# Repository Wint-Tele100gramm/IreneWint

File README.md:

# Руслана: голосовой помощник для умного дома

Офлайн-помощник на основе [Irene Voice Assistant](https://github.com/janvarev/Irene-Voice-Assistant) (Владислав Январёв);
до переработки проект назывался «Ирина».
Сервер — ТВ-приставка на Armbian (S905 с 1 ГБ, RK3528 с 2 ГБ) или компьютер с Windows/Linux. В комнатах — клиенты на ESP32
с микрофоном и усилителем: распознавание и синтез речи идут на сервере, ответ звучит в той комнате, откуда спросили.

Распознавание (Vosk через sherpa-onnx) и голос (Silero) работают без интернета. Интернет нужен Яндекс Музыке, погоде
и нейросети Gemini.

## Что внутри

| Часть | Файлы | Что делает |
|---|---|---|
| Сервер комнат | `runva_rooms.py` | Клиенты ESP32 по WebSocket, распознавание, выбор комнаты, ответы в комнату |
| Веб-интерфейс | `web_ui.py`, `web/index.html` | Комнаты, команды, сценарии, настройки, журнал — `http://<IP сервера>:8765/` |
| Ядро | `vacore.py`, `jaa.py` | Плагины, команды, диалоги, таймеры, озвучка |
| Клиент комнаты | `esp32_client/` | Прошивка ESP32 / ESP32-S3 (Arduino IDE) |
| Плата клиента | `hardware/irene-client/` | Проект KiCad, Gerber, схема и перечень элементов: ESP32-S3 + PCM5102A + PAM8403 + 2 микрофона на одной плате 68×58 мм, детали с одной стороны |
| Мультирум | `utils/multiroom.py`, `scripts/rk3528/snapserver.conf` | Snapcast: две линии музыки, какая комната что слушает |
| Установка | `scripts/rk3528/install.sh`, `install_windows.bat`, `ruslana/` | Приставка / Windows / дополнение Home Assistant OS |

Плагины (`plugins/`, каждый — отдельный файл, лишний можно просто удалить):

| Плагин | Команды и назначение |
|---|---|
| `plugin_homeassistant` | «включи свет на кухне», «выключи весь свет», «яркость в спальне тридцать», «закрой шторы», «какая температура в детской», «сцена кино» |
| `plugin_yandex_music` | «включи музыку», «включи исполнителя …», «пауза», «дальше», «что играет», «лайк»; по комнатам: «добавь кухню», «как в спальне», «перенеси музыку на кухню», «выключи музыку везде» |
| `plugin_scenes` | свои фразы и сценарии из нескольких команд |
| `plugin_weather` | «какая погода», «погода на завтра», «на послезавтра», «в субботу», «на выходные», «прогноз на неделю», «сколько градусов на улице» — Open-Meteo, нужен интернет |
| `plugin_jokes` | «расскажи анекдот», «ещё анекдот»; «пошлый анекдот», «взрослый анекдот», «анекдот для взрослых» |
| `plugin_gemini` | всё, что не команда: «расскажи сказку про ёжика», «почему небо голубое», «а что было дальше?»; «спроси нейросеть …», «забудь разговор», «расход нейросети» — Google Gemini, бесплатный или платный тариф |
| `plugin_timer` | «таймер на пять минут», «сколько осталось», «отмени таймер» |
| `plugin_datetime` | «который час», «какое сегодня число» |
| `plugin_rooms` | «объяви …» (во всех комнатах), «громкость голоса тридцать», «какая это комната» |
| `plugin_audio_sources` | «режим сопряжения», «блютуз на кухне» — звук с телефона (Bluetooth, DLNA) по комнатам (Linux) |
| `plugin_greetings`, `plugin_random`, `plugin_gamemoreless`, `plugin_voiceover` | «привет», «подбрось монетку», игра «больше-меньше», «скажи …» |
| `plugin_tts_silero`, `plugin_tts_console` | голос Silero; текст в консоль, если голос не загрузился |
| `plugin_fuzzy` | нечёткое сравнение команд: «вкличи свет», «какая пагода», «включи мою вону» — находит ближайшую команду (настройки: `options/plugin_fuzzy.json`, порог `threshold`) |
| `plugin_playwav_aplay`, `plugin_playwav_sounddevice` | проигрывание на Linux / Windows |
| `plugin_normalizer_prepare` | числа, латиница и символы — в слова для озвучки |

Как написать свой плагин: [docs/PLUGINS.md](docs/PLUGINS.md).
Из форка [AlexeyBond](https://github.com/AlexeyBond/Irene-Voice-Assistant) взяты идеи диалогов на генераторах, сценариев,
очистки кэша озвучки, записи звука для отладки и произношение времени с падежами (`utils/ru_speech`).

## Установка

**Приставка (Armbian/Debian, aarch64):**
```bash
git clone -b rk3528 https://github.com/Wint-Tele100gramm/IreneWint.git ~/irene
cd ~/irene
bash scripts/rk3528/install.sh     # Python берётся системный (3.10+) или PYTHON=/путь/к/python3
```
Параметры: `--no-bt`, `--no-dlna`, `--no-multiroom`, `--aec` (эхоподавление), `--lite` / `--full`.
Повторный запуск обновляет установку (AirPlay от прежних версий удаляется).
Python должен быть собран с `ssl`, `ctypes`, `sqlite3` — скрипт это проверит.

**Windows 10/11:** [README_WINDOWS.md](README_WINDOWS.md).

**Home Assistant OS (дополнение):** Настройки → Дополнения → Магазин дополнений → ⋮ → Репозитории →
`https://github.com/Wint-Tele100gramm/IreneWint#rk3528`, затем установить «Руслана». Сервер работает на машине
с Home Assistant, устройства Home Assistant подключаются сами, веб-интерфейс — в боковой панели. Подробно и чем
отличается от приставки — [ruslana/DOCS.md](ruslana/DOCS.md).

Дальше всё настраивается в веб-интерфейсе `http://<IP сервера>:8765/` (пароль — ключ клиентов,
`token` в `options/rooms.json`; установщик его покажет).

**Где настройки.** Все — в папке `options/`: `core.json` (ассистент), `rooms.json` (сервер комнат и ключ клиентов),
`plugin_*.json` (по файлу на плагин). Значения по умолчанию заданы в коде; файлы создаются сами при первом запуске
и хранят только ваши настройки — менять их удобнее на странице Русланы. Папка `options/` не попадает в git
(в ней токены), обновление `git pull` её не трогает.

## Веб-интерфейс

- **Комнаты** — клиенты на связи, прошивка, Wi-Fi, обрывы, причина перезагрузки; назначение комнаты (зоны Home Assistant
  из списка), громкость голоса, уровни речи; у микрофона самого сервера — усиление и живой индикатор.
  Сверху — что играет на линиях музыки; в карточке комнаты — какую линию она слушает и громкость музыки.
  Внизу — «Прошивка клиентов»: загрузить `IreneClient.ino.bin` и обновить клиенты по Wi-Fi (с откатом, если не заработает).
- **Команды** — команда текстом в любой комнате, последние услышанные фразы, список команд.
- **Сценарии** — редактор сценариев и своих фраз, работает сразу.
- **Настройки** — имена помощника, голос («Послушать»), Home Assistant, вход в Яндекс Музыку по коду
  (только с правами Музыки), время, таймер, сервер. Нужен перезапуск — появится кнопка.
- **Журнал** — события сервера, выбор устройств Home Assistant, записи фраз.

Страница для домашней сети: порт 8765 в интернет не открывайте. Выключить: `"web_ui": false` в `options/rooms.json`.

## Home Assistant

Токен: HA → Профиль → Безопасность → Долгосрочные токены доступа. Адрес и токен — в «Настройках» веб-интерфейса.

- Устройства ищутся по имени и зоне HA. Если названа комната, поиск идёт только в этой зоне; реле света ZHA (домен
  `switch`) тоже считаются светом. Что именно выбрано — видно в «Журнале».
- Без комнаты в команде берётся комната клиента: «включи свет» в спальне включит свет в зоне «Спальня».
- Одинаковые устройства в разных комнатах — Руслана переспросит: «Люстру где: Кухня или Спальня?»
- Устройство без связи (Zigbee) — Руслана так и скажет, а не отчитается впустую.
- Неудобное имя — синоним в `options/plugin_homeassistant.json`:
  `"aliases": { "ночник": "light.0x00158d0001a2b3c4", "свет в зале": ["light.a", "light.b"] }`.

## Погода

Плагин `plugin_weather` берёт прогноз с [Open-Meteo](https://open-meteo.com/): бесплатно, без ключа и регистрации,
но нужен интернет. В «Настройках» веб-интерфейса (раздел «Погода») укажите город — координаты найдутся сами
при первом вопросе — или широту и долготу дома (Яндекс Карты: правый клик по дому). Прогноз хранится
15 минут; если сервер недоступен, Руслана ответит по последнему прогнозу (не старше 6 часов).

Что можно спросить: «какая погода» (сейчас и на сегодня), «погода сегодня», «погода на завтра»,
«на послезавтра», «погода в пятницу», «в следующий понедельник», «на выходные», «прогноз на неделю»,
«сколько градусов на улице», «будет ли дождь завтра».

## Анекдоты

Плагин `plugin_jokes`: «расскажи анекдот» — обычный, «пошлый анекдот», «взрослый анекдот», «анекдот для
взрослых» — пошлый. «Ещё анекдот» сразу после пошлого — ещё пошлый. Руслана не повторяется, пока не расскажет
все анекдоты набора.

Анекдоты скачивает `scripts/get_jokes.py` (его вызывает `install.sh`; вручную:
`.venv/bin/python scripts/get_jokes.py`) в `data/jokes.json`. Источник — датасет
[igorktech/anekdots](https://huggingface.co/datasets/igorktech/anekdots) (лицензия ODC-BY, тексты с anekdot.ru),
самые высоко оценённые читателями; запасной — rzhunemogu.ru (`--source rzhunemogu`). Обычные и пошлые
разделяются по словам-признакам (мат — тоже в пошлые). Отбрасываются пошлые анекдоты, где есть дети,
анекдоты на национальные и прочие оскорбительные стереотипы, слишком длинные и с латиницей.
Сколько брать: `--normal 5000 --adult 2000`.

Hugging Face помечает этот датасет как «Not-For-All-Audiences» и без входа в аккаунт может его не отдать.
Тогда скачайте файл вручную (на странице датасета нажмите «View content», вкладка «Files», файл `anekdots.json`
или parquet-файл, сконвертированный в JSON), положите его на приставку, например в `data/anekdots.json`,
и запустите `.venv/bin/python scripts/get_jokes.py --file data/anekdots.json`. Подходят JSON-массив, JSON Lines,
«словарь столбцов» (`{'total_mark': [...], 'text': [...]}`, в том числе с кавычками Python) и `.gz`; файл читается потоком, памяти нужно ~50 МБ.

Пошлые можно выключить совсем или только в некоторых комнатах (раздел «Анекдоты» в «Настройках»).

## Нейросеть (Gemini)

Плагин `plugin_gemini` отвечает на фразы, для которых у Русланы нет команды: сказки, вопросы, разговор.
Команды (свет, музыка, таймер, погода…) по-прежнему выполняет сама Руслана, нейросеть их не перехватывает.
Явно: «спроси нейросеть …». Настройки — «Настройки» → «Нейросеть (Gemini)».

- Ключ: [aistudio.google.com/apikey](https://aistudio.google.com/apikey).
- Из России Google API отвечает «User location is not supported»: нужен прокси в другой стране
  (`socks5h://адрес:порт` или `http://адрес:порт`) или свой ретранслятор в поле «Адрес API».
- **Бесплатный тариф**: ограничение запросов в минуту и в день; когда лимит основной модели исчерпан, Руслана
  повторяет вопрос запасной (`gemini-flash-lite-latest`). Google может использовать такие запросы для обучения.
- **Платный тариф**: в AI Studio привязать к проекту ключа платёжный аккаунт (Billing) и выбрать «Платный»
  в настройках. Лимиты выше, можно взять модель сильнее (например Pro) и включить «размышления», запросы
  не идут в обучение. Расход токенов считается по месяцам (`data/gemini_usage.json`, «Руслана, расход нейросети»),
  есть месячный лимит. Подписка Google AI Pro / Gemini Advanced — для приложения Gemini, к API отношения не имеет.
- Ответ звучит в той комнате, где спросили, по предложениям; пока нейросеть думает, другие команды работают.
  Если ответа нет дольше 3 с, Руслана скажет «Сейчас подумаю».
- Разговор помнится 5 минут по каждой комнате: «а что было дальше?». «Забудь разговор» — сначала.
- Вопрос и ответ видны в «Журнале». Текст запросов уходит в Google.

## Яндекс Музыка

Вход — кнопкой в «Настройках» (код вводится на ya.ru/device) или `.venv/bin/python scripts/rk3528/yandex_token.py`.
Запрашиваются только права Музыки. Нужна подписка Плюс. Пока Руслана слушает команду или отвечает, музыка приглушается.

### Музыка по комнатам (мультирум)

Snapcast (ставит `install.sh`) держит **две независимые линии музыки**: например, у вас в комнате одна, у жены — другая.
Комнаты с музыкой — клиенты ESP32 с прошивкой 3.1+ и динамик приставки (snapclient с ID `local`). В одной линии
комнаты играют синхронно. Звук — 44100 Гц стерео (≈1,4 Мбит/с Wi-Fi на комнату), задержка 0,6 с: пауза и «стоп»
слышны сразу (клиенты приглушаются мгновенно), «дальше» — меньше чем через секунду.

После обновления с прошивки 3.0: `git pull && bash scripts/rk3528/install.sh` (новый `snapserver.conf`) и прошивка 3.1
во всех клиентах — старая стерео-поток не играет. Если в комнатах прерывается музыка, в
`~/.config/irene/snapserver.conf` увеличьте `buffer` до 1000.

| Сказать | Что будет |
|---|---|
| «включи музыку», «поставь кино» | играет там, где сказали. Если здесь уже играла своя музыка — заменяется |
| «включи музыку на кухне», «…везде» | в названных комнатах (если здесь уже играет — комнаты подключаются к этой музыке) |
| «добавь кухню», «и в спальне», «музыку везде» | комнаты подключаются к музыке этой комнаты |
| «как на кухне», «то же, что в спальне» | эта комната слушает то же, что там |
| «перенеси музыку на кухню» | музыка уходит отсюда туда |
| «выключи музыку» | здесь (если эту музыку слушают и в других комнатах — они продолжают) |
| «выключи музыку на кухне», «…везде», «выключи всю музыку» | там / везде |
| «где играет музыка» | что играет на каждой линии и в каких комнатах |
| «громче», «тише», «громкость тридцать» | громкость музыки в этой комнате |
| «пауза», «дальше», «что играет», «лайк» | для музыки этой комнаты (или единственной играющей) |

Обе линии заняты, а новую музыку просят в третьей комнате — Руслана скажет, что где играет, и предложит «как на …».
То же самое — на странице «Комнаты». Без snapserver (Windows, `--no-multiroom`) музыка играет на динамике сервера.

Клиенты старых прошивок (до 3.1) музыку не играют. На ESP32-S3 с прошивкой 3.1 эхоподавление убирает музыку из микрофона;
на обычном ESP32 микрофон слышит её:
говорите «Руслана» громче музыки — после имени музыка в комнате притихнет до конца команды.

## Звук с телефона (приставка)

| Откуда | Как |
|---|---|
| Android и iOS | «Руслана, режим сопряжения» → в Bluetooth телефона выбрать **Ruslana** (3 минуты) |
| Android | Приложение с DLNA/UPnP (BubbleUPnP, Hi-Fi Cast) → «Руслана» |

С мультирумом звук с телефона идёт не в динамик приставки, а в третью линию — **«Телефон»** (поток `phone`
в snapserver; PipeWire получает выход «Ruslana-rooms», и всё, что приходит по Bluetooth и DLNA, перенаправляется в него):

- телефон заиграл — звук идёт в комнату, где сказали «режим сопряжения» (или туда, где слушали в прошлый раз);
- «Руслана, блютуз на кухне», «телефон везде», «музыку с телефона» — подключить комнаты; «добавь спальню»,
  «как на кухне», «выключи музыку» — как с Яндекс Музыкой; на странице «Комнаты» — линия «Телефон»;
- «пауза», «продолжи», «дальше», «назад», «что играет» — управляют телефоном по Bluetooth (AVRCP);
- телефон молчит 20 секунд — комнаты линии выключаются.

Нужна новая настройка snapserver: после обновления запустите `bash scripts/rk3528/install.sh`. Если PipeWire не создаст
выход (в журнале «не создал выход в комнаты»), звук с телефона играет на динамике приставки, как раньше.

Встроенный Bluetooth приставок часто не поддерживается ядром Armbian — подойдёт USB-донгл (RTL8761B).

## Комнаты

- Клиент: [esp32_client/README.md](esp32_client/README.md). Название комнаты = зона в Home Assistant
  (можно назначить на странице «Комнаты», не трогая клиент).
- Одну фразу услышали несколько клиентов — ответит тот, где громче; команда выполнится один раз.
- Таймеры и их сигнал звучат в той комнате, где их поставили; если клиент отключился — во всех комнатах.
- Микрофон самого сервера тоже может быть комнатой: «Микрофон приставки как комната» в настройках.
- Распознавание работает, только пока в комнате говорят — 5–6 комнат не нагружают сервер постоянно.

### Сценарии

На странице «Сценарии» или в `options/plugin_scenes.json`:
```json
{
    "aliases": { "зажги|сделай светло": "включи свет" },
    "scenes": {
        "спокойной ночи": ["выключи весь свет", "выключи музыку", "скажи: Спокойной ночи!"],
        "доброе утро": ["включи свет на кухне", "время", "какая погода", "включи музыку"]
    },
    "quiet_steps": true
}
```
Шаг — любая команда, `скажи: текст` или `пауза: секунды`. Свои фразы важнее одноимённых встроенных команд.

### Диалоги в своих плагинах

Команда может вернуть генератор: `answer = yield "Вопрос?"` (или `yield ("Вопрос?", 15)` с таймаутом).
Ответ ждётся без имени и в той же комнате; без ответа в генератор придёт `DialogTimeout` (`from vacore import DialogTimeout`).

## Распознавание, голос, кэш

- Распознавание: малая потоковая модель Vosk int8 — ~100 МБ ОЗУ на все комнаты.
  `bash scripts/rk3528/get_asr_model.sh full` — полная 0.56 (~250 МБ ОЗУ, точнее; для 2 ГБ и больше).
- Голос: Silero TTS (`v5_5_ru`, PyTorch): естественная речь с ударениями, «ё», омографами и вопросительной
  интонацией. Голоса xenia, baya, kseniya (женские), aidar, eugene (мужские) — на странице Русланы, раздел «Голос».
  Ставит `install.sh` (`scripts/rk3528/get_tts_silero.sh`: PyTorch для процессора и модель в `models/silero`),
  скорость на этой машине: `.venv/bin/python scripts/tts_bench.py --threads 2 3` при остановленной Руслане.
  Ответ звучит по предложениям: первое начинает играть, пока синтезируются следующие.
  Память — 450–650 МБ; на 1 ГБ работает со сжатой подкачкой zram. Лицензия моделей — CC BY-NC 4.0 (для дома можно).
- Частота процессора: пока клиент передаёт фразу и пока синтезируется ответ, регулятор частоты переключается
  на `performance` (ядра сразу на максимуме), через 3 с после речи возвращается прежний (ondemand / schedutil).
  Права на это даёт `install.sh` (`/etc/tmpfiles.d/irene-cpufreq.conf`). Выключить или изменить задержку —
  «Настройки» → «Сервер и клиенты». Проверить: `watch -n0.5 cat /sys/devices/system/cpu/cpufreq/policy0/scaling_governor`.
- Кэш ответов (`tts_cache/`) чистится раз в 6 часов: не больше 300 МБ и без фраз, не звучавших 90 дней.
- Запись фраз для отладки: «Записывать фразы в WAV» в настройках — слушать на вкладке «Журнал».

## Эхоподавление на приставке

```bash
bash scripts/rk3528/enable_aec.sh        # включить
bash scripts/rk3528/enable_aec.sh off    # выключить
```
PipeWire вычитает звук динамика из микрофона приставки: Руслану можно перебить («стоп», «хватит»), а «Руслана, …» слышно поверх
музыки. Перед включением выберите реальные микрофон и динамик по умолчанию (`pactl set-default-source/sink`).

## Приставка с 1 ГБ ОЗУ

`install.sh` сам включает облегчённый режим при ОЗУ меньше 1,5 ГБ: без DLNA и Bluetooth, zram-подкачка, лимит памяти
Русланы 800 МБ. Ориентировочно: распознавание ~100 МБ, голос ~250 МБ, mpv (на каждую играющую линию) ~40 МБ,
PipeWire + snapserver + snapclient ~60 МБ.

## Управление

```bash
systemctl --user restart irene          # перезапуск (или кнопкой в веб-интерфейсе)
journalctl --user-unit irene -f         # логи
systemctl --user status irene-snapserver irene-snapclient   # мультирум
.venv/bin/python scripts/rk3528/irene_cmd.py "руслана который час"   # команда текстом из консоли
```

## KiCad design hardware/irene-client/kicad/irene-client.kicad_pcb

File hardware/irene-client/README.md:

# Плата клиента Русланы v3

Весь клиент на одной двухсторонней плате **68×58 мм**: ESP32-S3, стереоЦАП PCM5102A, усилитель PAM8403 2×3 Вт,
разъёмы для двух микрофонов INMP441. **Все детали — на верхней стороне** (SMD и штыри в отверстия), нижний слой —
земля и немногие перемычки. Питание 5 В на штыри, все стабилизаторы и фильтры на плате. Разъёма USB нет: первая
прошивка — проводами к выводам модуля, дальше — по Wi-Fi.

Версия 3 рассчитана на изготовление и дома (ЛУТ, фоторезист):

| | v2 | v3 |
|---|---|---|
| Размер | 50×42 мм | 68×58 мм |
| Детали | с обеих сторон | только сверху |
| Дорожки | 0,25–0,6 мм | сигналы 0,6 мм, питание 0,8 мм (≈70 % длины не уже 0,6 мм) |
| Зазор | 0,2 мм | 0,4 мм (кроме выводов ЦАП и LP5907, см. ниже) |
| Переходы | 58 + 26 сшивки земли, 0,6/0,3 мм | 34, 1,4/0,6 мм — под проволочную перемычку |
| Переходы под деталями | были | нет ни одного |
| Медь меньше 1 мм² и островки без земли | были | убраны |

| Сверху | Снизу |
|---|---|
|  |  |

Картинки сделаны из готовых Gerber-файлов (вид снизу — зеркальный, как если перевернуть плату).

## Файлы

| Файл | Что это |
|---|---|
| `kicad/` | **проект KiCad**: схема, плата с разводкой и заливками, правила (зазоры) |
| `irene-client.lay6` | **плата для Sprint Layout 6** (см. ниже) |
| `irene-client-gerber.zip` | Gerber + сверловка, собранные генератором (для заказа без KiCad) |
| `schematic.pdf` | принципиальная схема (A3) |
| `img/assembly-top.png`, `img/assembly-bottom.png` | сборочный чертёж: где какая деталь, номиналы, первый вывод — красная точка |
| `bom.csv` | перечень элементов (Excel, разделитель «;») |
| `bom-jlcpcb.csv`, `cpl-jlcpcb.csv` | перечень и координаты деталей (обе стороны) в формате JLCPCB для заводского монтажа |

## Проект KiCad

Открыть `kicad/irene-client.kicad_pro` в KiCad 7, 8 или 9 (проект в формате KiCad 6, новая версия сама предложит его
обновить). Библиотеки ставить не нужно: символы и посадочные места лежат внутри файлов.

1. **Плата** (`irene-client.kicad_pcb`): нажать **B** — KiCad зальёт землю на обоих слоях (заливки заданы, но в файле не
   залиты). Затем «Проверка → Проверка правил проектирования (DRC)».
2. **Правила** (класс Default и файл `irene-client.kicad_dru`): зазор между дорожками, площадками и переходами разных
   цепей — 0,4 мм. Исключения — выводы с мелким шагом: у PCM5102A (TSSOP, шаг 0,65 мм) и LP5907 (SOT-23-5) зазор до
   выводов 0,2 мм, между дорожками цепей ЦАП у его выводов — 0,3 мм; дорожки к выводам ЦАП — 0,3 мм (шире вывода
   не бывают). Ширина остальных: сигналы 0,6 мм, питание 5 В и динамики — 0,8 мм; там, где 0,6 мм не помещается
   (около ЦАП, между выводами), дорожка уже — но не уже 0,3 мм. Переходы 1,4/0,6 мм, ни одного под корпусами деталей
   (это проверяет генератор по контуру корпуса — в правилах KiCad по курсу этого не выразить).
3. **Gerber**: «Файл → Изготовление → Gerber» (слои F/B.Cu, F/B.Paste, F/B.Silkscreen, F/B.Mask, Edge.Cuts) и
   «Сверловка» — сжать в zip и загрузить на сайт фабрики.
4. Схема (`irene-client.kicad_sch`) связана с платой: «Обновить плату по схеме» (F8) не должна предлагать изменений,
   кроме служебных.

## Sprint Layout 6

`irene-client.lay6` — та же плата для Sprint Layout 6.0: детали как компоненты (позиционное обозначение и номинал —
в свойствах детали), площадки, дорожки, переходы, шелкография с подписями, контур, запрет массива под антенной.

- Заливка земли — «массив» Sprint Layout, включён на обоих слоях; Sprint Layout рассчитывает его сам.
  Дорожки, переходы и SMD-выводы цепи GND подключены к массиву сплошь, выводы штырей — термобарьером 0,5 мм,
  у остальных объектов зазор до массива 0,4 мм.
- Там, где генератор убрал медь (островки без связи с землёй и куски меньше 1 мм²), стоят вырезы массива —
  Sprint Layout их не зальёт. Земля разведена и дорожками, поэтому связь всех её выводов от массива не зависит.
- Цепей (связей) в формате Sprint Layout нет — только медь; соединения проверены в генераторе.
- Файл собран по описанию формата из KiCad (импорт Sprint Layout); чтение и запись сверены побайтово с файлами,
  сохранёнными самим Sprint Layout, но в самой программе файл не открывался. Если что-то откроется не так —
  в Sprint Layout 6 есть «Файл → Импорт → Gerber»: подойдут файлы из `irene-client-gerber.zip`.

## Штыри на плате

| Разъём | Выводы (по шелкографии) | Что подключать |
|---|---|---|
| J1 | 5V, G | блок питания 5 В, 2 А (5V — квадратная площадка) |
| J5 | R+ R− L− L+ | динамики 4–8 Ом. Минусы динамиков с землёй **не соединять** (выходы мостовые) |
| J3 «MIC1» | G V SD SC WS G | микрофон 1 INMP441: GND, VDD, SD, SCK, WS, L/R (L/R уже на земле) |
| J4 «MIC2» | G V SD SC WS V | микрофон 2 INMP441: то же, L/R уже на 3,3 В (правый канал). Разъём повёрнут: вывод 1 (G) — снизу |

Провода к микрофонам — до 20–30 см, лучше витой парой или в общей оплётке с землёй.

## Первая прошивка без USB-разъёма

Подпаяться тонкими проводами к выводам модуля U1 (нумерация — по сборочному чертежу, вывод 1 — красная точка):

- **через USB**: вывод 14 — D+ (зелёный провод USB), вывод 13 — D− (белый), земля — любой вывод G, питание — 5 В на J1.
  В Arduino IDE: плата «ESP32S3 Dev Module», **USB CDC On Boot: Enabled**, остальное — как в `esp32_client/README.md`;
- **или через переходник USB-UART на 3,3 В**: вывод 37 (TXD0) → RX переходника, вывод 36 (RXD0) → TX, GND → GND.

Вход в загрузчик: держать BOOT, нажать и отпустить RST, отпустить BOOT. После первой прошивки провода снять —
дальше обновления идут по воздуху («Прошивка клиентов» в веб-интерфейсе сервера).

## Схема вкратце

- **Вход 5 В**: самовосстанавливающийся предохранитель 2 А → защита от переполюсовки (P-MOSFET AO3401A) →
  TVS-диод 6 В → 220 мкФ.
- **3,3 В для ESP32 и микрофонов** — AMS1117-3.3; микрофоны дополнительно через RC-фильтр 10 Ом + 10 мкФ.
- **3,3 В для аналоговой части ЦАП** — отдельный малошумящий LP5907; цифровая часть ЦАП — через ферритовую бусину.
- **Усилитель** питается отдельной веткой: дроссель 4,7 мкГн + 470 мкФ рядом с микросхемой. Импульсный ток
  усилителя не идёт через цифровую часть — то, что раньше давал аккумулятор 18650.
- **Земля** — дорожками ко всем выводам и заливка поверх на обоих слоях; под ЦАП и усилителем — дорожка по оси корпуса
  от их земляных выводов. Под антенной модуля меди нет на обоих слоях.
- **ЦАП и усилитель включает прошивка** (GPIO 17 → XSMT ЦАП и SHDN усилителя): в тишине они выключены — нет шипения.
- Делитель 10к/1,2к на входе PAM8403: полной громкости соответствует почти полная мощность усилителя без перегрузки.

GPIO: микрофоны SCK 4, WS 5, SD 6; ЦАП DIN 7, BCK 15, LRCK 16; включение ЦАП и усилителя 17; светодиод 18;
кнопка BOOT — GPIO 0. Те же, что в прошивке (`esp32_client/IreneClient/config.h`, с версии 3.4).

## Заказ и сборка

- **Заказ**: 2 слоя, 1,6 мм, 68×58 мм; минимальная дорожка 0,3 мм, зазор 0,2 мм (у выводов ЦАП), отверстия от 0,6 мм.
  Покрытие HASL lead free или ENIG.
- **Дома** (ЛУТ / фоторезист): вывод на плёнку — из Gerber или из Sprint Layout. Переходы — проволочные перемычки
  (отверстие 0,6 мм, площадка 1,4 мм): все стоят вне корпусов деталей, их можно паять до установки деталей.
  Самое тонкое место — веер дорожек 0,3 мм у ЦАП (шаг выводов 0,65 мм).
- **Заводской монтаж** (по желанию): загрузить `bom-jlcpcb.csv` и `cpl-jlcpcb.csv`, монтаж с одной стороны (Top).
  Поворот деталей в предпросмотре иногда приходится поправить вручную.
- **Ручная сборка**: перемычки в переходах, затем микросхемы с мелким шагом (U3, U5), стабилизаторы, пассивные,
  дроссель, диод, электролиты, кнопки, модуль ESP32, в конце штыри.
  До установки модуля подать 5 В на J1 через резистор 10–20 Ом и проверить 3,3 В на выходах AMS1117 и LP5907.

## Как пересобрать

Всё генерируется скриптами из `hardware/gen` (детали и цепи — `design.py`, расстановка — `placement.py`):

```
IRENE_PCB_EXT=<папка с kiutils, библиотеками KiCad и freerouting> python3 hardware/gen/build.py [--route] [--reuse]
```

Скрипт сам проверяет результат: связность всех цепей и отсутствие замыканий — по готовым Gerber; зазоры — по разводке;
цепи схемы KiCad — по сравнению с `design.py`.

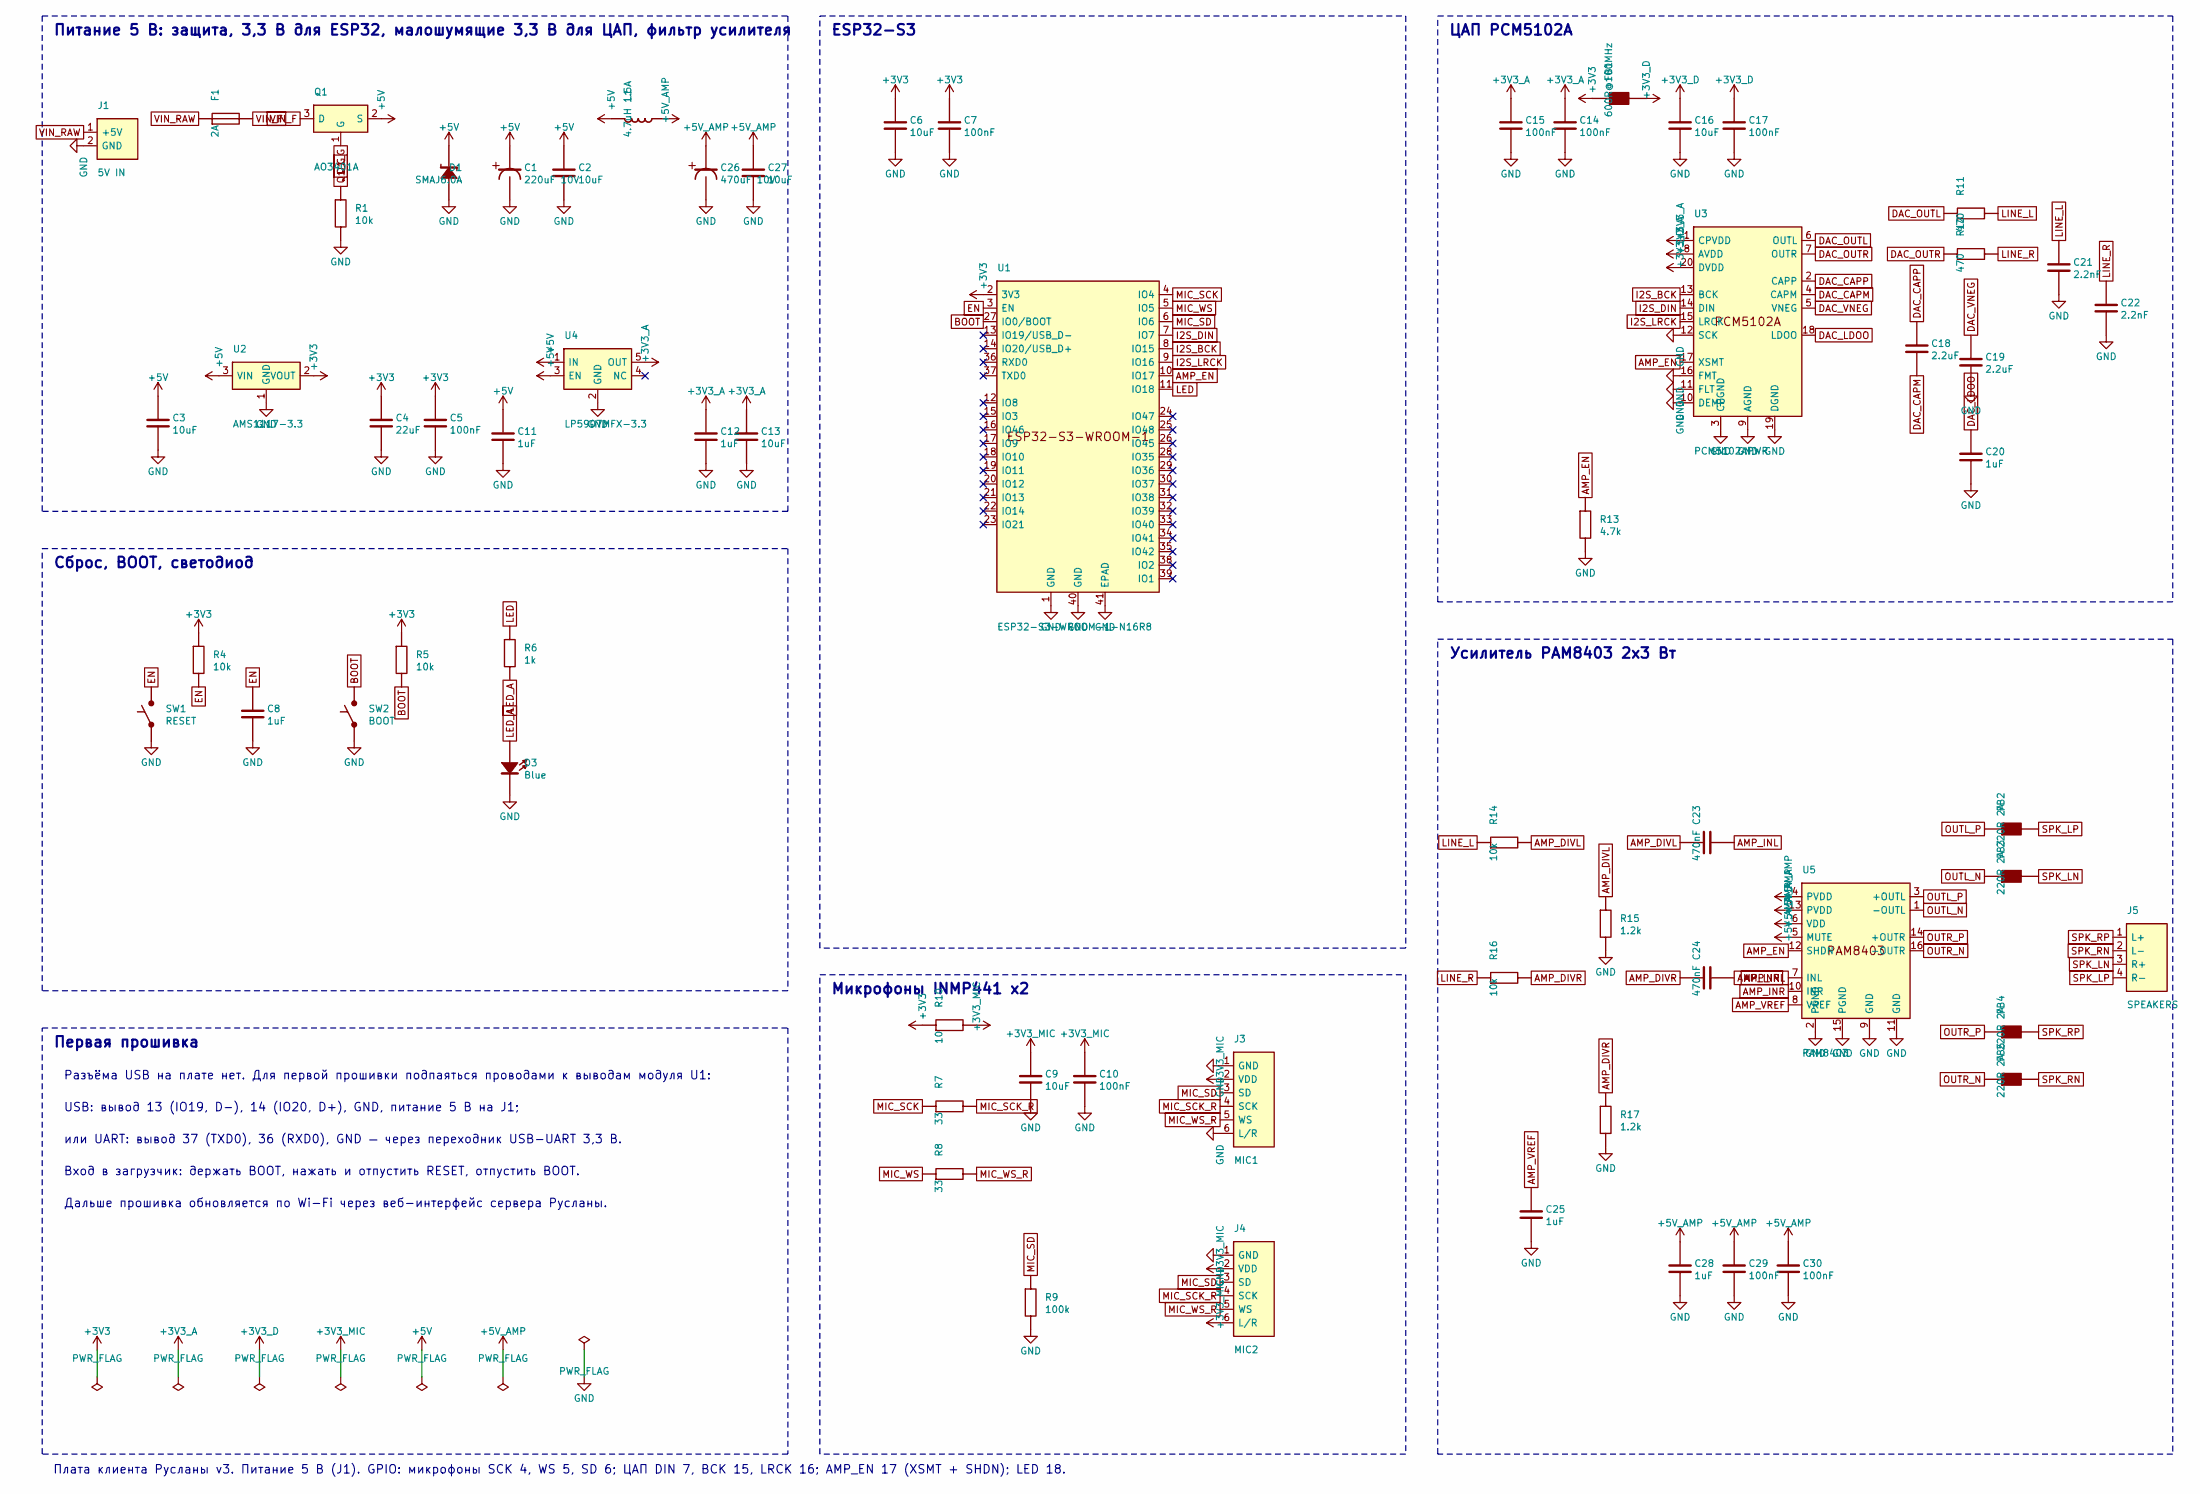
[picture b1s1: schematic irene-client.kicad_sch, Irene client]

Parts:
C1: 220uF 10V; CP_Elec_6.3x7.7
C2, C3, C6, C9, C13, C16, C27: 10uF; C_0805_2012Metric
C4: 22uF; C_1206_3216Metric
C5, C7, C10, C14, C15, C17, C29, C30: 100nF; C_0603_1608Metric
C8, C11, C12, C20, C25, C28: 1uF; C_0603_1608Metric
C18, C19: 2.2uF; C_0603_1608Metric
C21, C22: 2.2nF; C_0603_1608Metric
C23, C24: 470nF; C_0603_1608Metric
C26: 470uF 10V; CP_Elec_8x10
D1: SMAJ6.0A; D_SMA
D3: Blue; LED_0603_1608Metric
F1: 2A; Fuse_1812_4532Metric
FB1: 600R@100MHz; L_0603_1608Metric
FB2, FB3, FB4, FB5: 220R 2A; L_0805_2012Metric
J1: 5V IN; PinHeader_1x02_P2.54mm_Vertical
J3: MIC1; PinHeader_1x06_P2.54mm_Vertical
J4: MIC2; PinHeader_1x06_P2.54mm_Vertical
J5: SPEAKERS; PinHeader_1x04_P2.54mm_Vertical
L1: 4.7uH 1.5A; L_Taiyo-Yuden_NR-40xx
Q1: AO3401A; SOT-23
R1, R4, R5, R14, R16: 10k; R_0603_1608Metric
R6: 1k; R_0603_1608Metric
R7, R8: 33; R_0603_1608Metric
R9: 100k; R_0603_1608Metric
R10: 10; R_0603_1608Metric
R11, R12: 470; R_0603_1608Metric
R13: 4.7k; R_0603_1608Metric
R15, R17: 1.2k; R_0603_1608Metric
SW1: RESET; SW_Push_1P1T_NO_CK_KMR2
SW2: BOOT; SW_Push_1P1T_NO_CK_KMR2
U1: ESP32-S3-WROOM-1-N16R8; ESP32-S3-WROOM-1
U2: AMS1117-3.3; SOT-223-3_TabPin2
U3: PCM5102APWR; TSSOP-20_4.4x6.5mm_P0.65mm
U4: LP5907MFX-3.3; SOT-23-5
U5: PAM8403; SOIC-16_3.9x9.9mm_P1.27mm

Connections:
+3V3: C4.1, C5.1, C6.1, C7.1, FB1.1, R4.1, R5.1, R10.1, U1.2 (3V3), U2.2 (VOUT)
+3V3_A: C12.1, C13.1, C14.1, C15.1, U3.1 (CPVDD), U3.8 (AVDD), U4.5 (OUT)
+3V3_D: C16.1, C17.1, FB1.2, U3.20 (DVDD)
+3V3_MIC: C9.1, C10.1, J3.2 (VDD), J4.2 (VDD), J4.6 (L/R), R10.2
+5V: C1.1, C2.1, C3.1, C11.1, D1.1, L1.1, Q1.2 (S), U2.3 (VIN), U4.1 (IN), U4.3 (EN)
+5V_AMP: C26.1, C27.1, C28.1, C29.1, C30.1, L1.2, U5.4 (PVDD), U5.5 (MUTE), U5.6 (VDD), U5.13 (PVDD)
AMP_DIVL: C23.1, R14.2, R15.1
AMP_DIVR: C24.1, R16.2, R17.1
AMP_EN: R13.1, U1.10 (IO17), U3.17 (XSMT), U5.12 (SHDN)
AMP_INL: C23.2, U5.7 (INL)
AMP_INR: C24.2, U5.10 (INR)
AMP_VREF: C25.1, U5.8 (VREF)
BOOT: R5.2, SW2.1, U1.27 (IO0/BOOT)
DAC_CAPM: C18.2, U3.4 (CAPM)
DAC_CAPP: C18.1, U3.2 (CAPP)
DAC_LDOO: C20.1, U3.18 (LDOO)
DAC_OUTL: R11.1, U3.6 (OUTL)
DAC_OUTR: R12.1, U3.7 (OUTR)
DAC_VNEG: C19.1, U3.5 (VNEG)
EN: C8.1, R4.2, SW1.1, U1.3 (EN)
GND: C1.2, C2.2, C3.2, C4.2, C5.2, C6.2, C7.2, C8.2, C9.2, C10.2, C11.2, C12.2, C13.2, C14.2, C15.2, C16.2, C17.2, C19.2, C20.2, C21.2, C22.2, C25.2, C26.2, C27.2, C28.2, C29.2, C30.2, D1.2, D3.1, J1.2 (GND), J3.1 (GND), J3.6 (L/R), J4.1 (GND), R1.2, R9.2, R13.2, R15.2, R17.2, SW1.2, SW2.2, U1.1 (GND), U1.40 (GND), U1.41 (EPAD), U2.1 (GND), U3.3 (CPGND), U3.9 (AGND), U3.10 (DEMP), U3.11 (FLT), U3.12 (SCK), U3.16 (FMT), U3.19 (DGND), U4.2 (GND), U5.2 (PGND), U5.9 (GND), U5.11 (GND), U5.15 (PGND)
I2S_BCK: U1.8 (IO15), U3.13 (BCK)
I2S_DIN: U1.7 (IO7), U3.14 (DIN)
I2S_LRCK: U1.9 (IO16), U3.15 (LRCK)
LED: R6.1, U1.11 (IO18)
LED_A: D3.2, R6.2
LINE_L: C21.1, R11.2, R14.1
LINE_R: C22.1, R12.2, R16.1
MIC_SCK: R7.1, U1.4 (IO4)
MIC_SCK_R: J3.4 (SCK), J4.4 (SCK), R7.2
MIC_SD: J3.3 (SD), J4.3 (SD), R9.1, U1.6 (IO6)
MIC_WS: R8.1, U1.5 (IO5)
MIC_WS_R: J3.5 (WS), J4.5 (WS), R8.2
OUTL_N: FB3.1, U5.1 (-OUTL)
OUTL_P: FB2.1, U5.3 (+OUTL)
OUTR_N: FB5.1, U5.16 (-OUTR)
OUTR_P: FB4.1, U5.14 (+OUTR)
Q1_G: Q1.1 (G), R1.1
SPK_LN: FB3.2, J5.3 (R+)
SPK_LP: FB2.2, J5.4 (R-)
SPK_RN: FB5.2, J5.2 (L-)
SPK_RP: FB4.2, J5.1 (L+)
VIN_F: F1.2, Q1.3 (D)
VIN_RAW: F1.1, J1.1 (+5V)

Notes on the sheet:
Питание 5 В: защита, 3,3 В для ESP32, малошумящие 3,3 В для ЦАП, фильтр усилителя
Сброс, BOOT, светодиод
Первая прошивка
ESP32-S3
Микрофоны INMP441 x2
ЦАП PCM5102A
Усилитель PAM8403 2x3 Вт
Плата клиента Русланы v3. Питание 5 В (J1). GPIO: микрофоны SCK 4, WS 5, SD 6; ЦАП DIN 7, BCK 15, LRCK 16; AMP_EN 17 (XSMT + SHDN); LED 18.
Разъёма USB на плате нет. Для первой прошивки подпаяться проводами к выводам модуля U1:
USB: вывод 13 (IO19, D-), 14 (IO20, D+), GND, питание 5 В на J1;
или UART: вывод 37 (TXD0), 36 (RXD0), GND — через переходник USB-UART 3,3 В.
Вход в загрузчик: держать BOOT, нажать и отпустить RESET, отпустить BOOT.
Дальше прошивка обновляется по Wi-Fi через веб-интерфейс сервера Русланы.

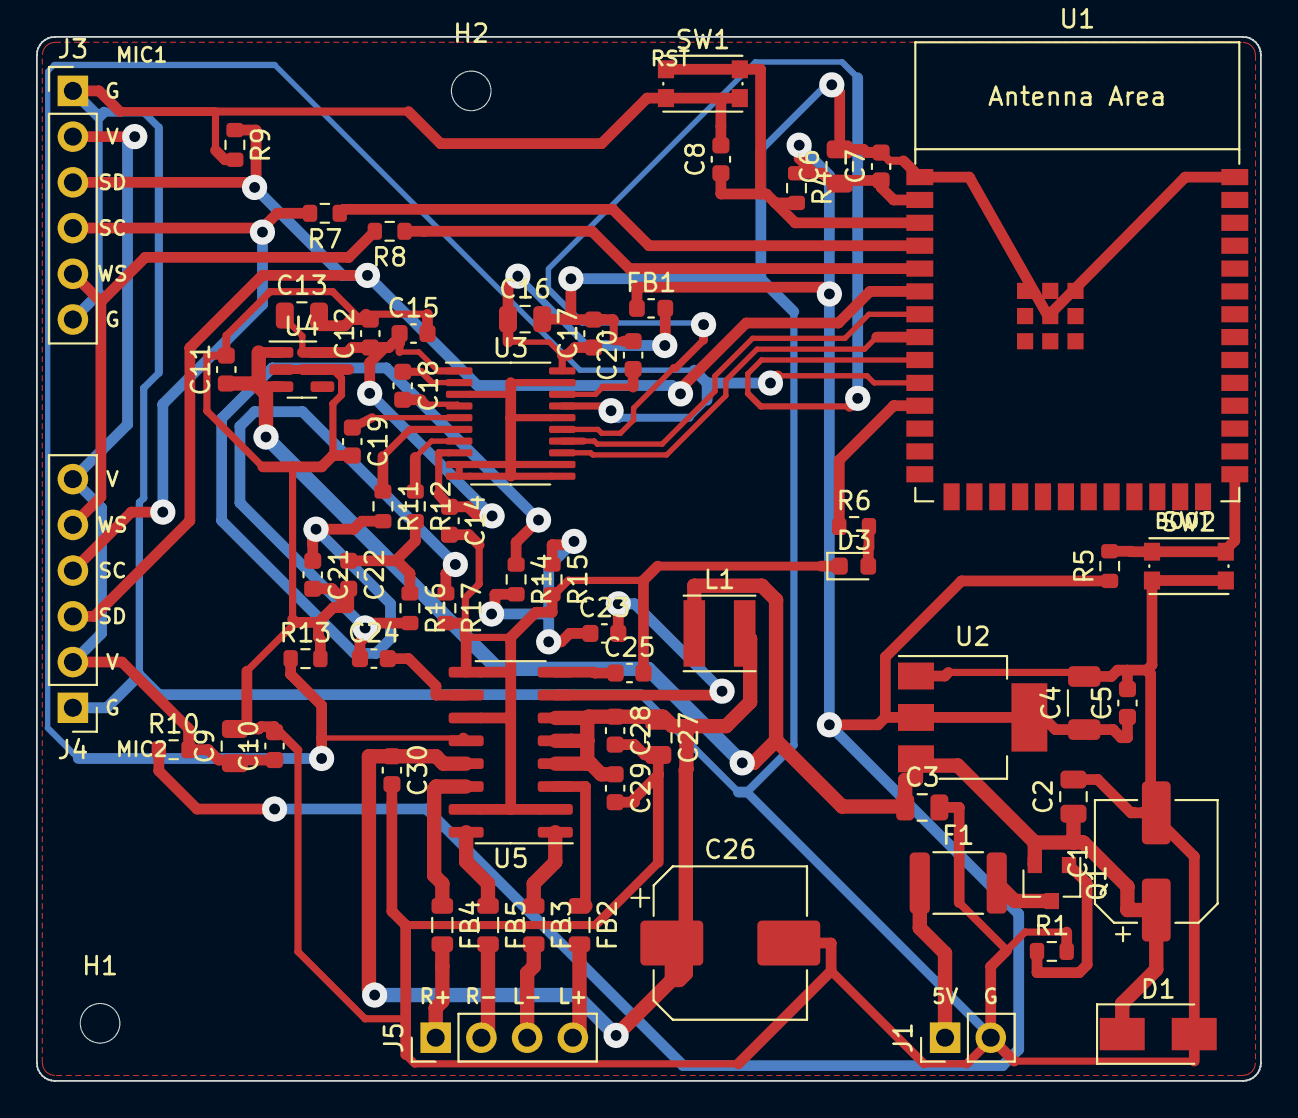
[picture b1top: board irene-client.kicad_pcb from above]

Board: 2 copper layers, 68.0 x 58.0 mm, 68 parts (0 on the bottom side), 44 nets.

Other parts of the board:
H1, H2: M2; MountingHole_2.2mm_M2

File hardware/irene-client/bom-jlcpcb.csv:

Comment,Designator,Footprint,LCSC Part #
220uF 10V,C1,CP_Elec_6.3x7.7,
10uF,"C2,C3,C6,C9,C13,C16,C27",C_0805_2012Metric,
22uF,C4,C_1206_3216Metric,
100nF,"C5,C7,C10,C14,C15,C17,C29,C30",C_0603_1608Metric,
1uF,"C8,C11,C12,C20,C25,C28",C_0603_1608Metric,
2.2uF,"C18,C19",C_0603_1608Metric,
2.2nF,"C21,C22",C_0603_1608Metric,
470nF,"C23,C24",C_0603_1608Metric,
470uF 10V,C26,CP_Elec_8x10,
SMAJ6.0A,D1,D_SMA,
Blue,D3,LED_0603_1608Metric,
2A,F1,Fuse_1812_4532Metric,
600R@100MHz,FB1,L_0603_1608Metric,
220R 2A,"FB2,FB3,FB4,FB5",L_0805_2012Metric,
5V IN,J1,PinHeader_1x02_P2.54mm_Vertical,
MIC1,J3,PinHeader_1x06_P2.54mm_Vertical,
MIC2,J4,PinHeader_1x06_P2.54mm_Vertical,
SPEAKERS,J5,PinHeader_1x04_P2.54mm_Vertical,
4.7uH 1.5A,L1,L_Taiyo-Yuden_NR-40xx,
AO3401A,Q1,SOT-23,
10k,"R1,R4,R5,R14,R16",R_0603_1608Metric,
1k,R6,R_0603_1608Metric,
33,"R7,R8",R_0603_1608Metric,
100k,R9,R_0603_1608Metric,
10,R10,R_0603_1608Metric,
470,"R11,R12",R_0603_1608Metric,
4.7k,R13,R_0603_1608Metric,
1.2k,"R15,R17",R_0603_1608Metric,
RESET,SW1,SW_Push_1P1T_NO_CK_KMR2,
BOOT,SW2,SW_Push_1P1T_NO_CK_KMR2,
ESP32-S3-WROOM-1-N16R8,U1,ESP32-S3-WROOM-1,
AMS1117-3.3,U2,SOT-223-3_TabPin2,
PCM5102APWR,U3,TSSOP-20_4.4x6.5mm_P0.65mm,
LP5907MFX-3.3,U4,SOT-23-5,
PAM8403,U5,SOIC-16_3.9x9.9mm_P1.27mm,

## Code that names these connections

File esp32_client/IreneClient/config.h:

// Распиновка и параметры клиента. Wi-Fi, адрес сервера и имя комнаты задаются
// через веб-портал при первом запуске (точка доступа "Ruslana-XXXXXX"), а не здесь.
// Усиление, порог и паузу потом удобнее менять в веб-интерфейсе сервера (вкладка «Комнаты»).
#pragma once

#define FW_VERSION "3.5"

// ---------------- распиновка ----------------
#if defined(CONFIG_IDF_TARGET_ESP32S3)
  // ESP32-S3 (модуль S3-N16R8 / ESP32-S3-WROOM-1 или плата DevKitC-1).
  // В адаптере для WROOM-32E эти выводы подписаны: SVP, SVN, IO34, IO35, IO32, IO33.
  // GPIO 35, 36, 37 заняты памятью PSRAM (модули R8) — ничего к ним не подключать.
  #define MIC_SCK   4    // INMP441 SCK          (адаптер: SVP)
  #define MIC_WS    5    // INMP441 WS           (адаптер: SVN)
  #define MIC_SD    6    // INMP441 SD           (адаптер: IO34)
  #define AMP_DIN   7    // DIN / SD (данные)    (адаптер: IO35) — MAX98357A DIN, PCM5102 DIN («SD»)
  #define AMP_BCLK  15   // BCLK / BCK           (адаптер: IO32)
  #define AMP_LRC   16   // LRC / LCK / LR       (адаптер: IO33)
  #define AMP_SD    17   // включение ЦАП и усилителя (PCM5102A XSMT + PAM8403 SHDN; на плате hardware/irene-client), без них — свободен
  #define LED_PIN   18   // светодиод «слушаю» (на плате hardware/irene-client; у адаптера «LED-IO4» — GPIO35/PSRAM, не трогать)
  #define AUDIO_BUF_BYTES (64 * 1024)   // буфер ответа (в PSRAM, если она есть)
  #define SNAP_RING_MS    2000          // очередь музыки, мс (в PSRAM): больше буфера snapserver (600 мс) с запасом
  #define AMP_RATE        44100         // частота вывода
  #define AMP_STEREO      1             // 1 — стерео (PCM5102 и т.п.), 0 — один динамик: L+R в оба канала
  #define MIC_AEC         1             // эхо- и шумоподавление ESP-SR (только S3)
  #define MIC_COUNT       2             // микрофонов INMP441 на одной шине: 1 или 2 (второй — L/R на 3V3).
                                        // С двумя — решётка ESP-SR (выделяет голос); если второго нет или он
                                        // молчит, клиент сам работает с одним
#else
  // ESP32 DevKit (WROOM-32)
  #define MIC_SCK   32
  #define MIC_WS    25
  #define MIC_SD    33
  #define AMP_BCLK  26
  #define AMP_LRC   27
  #define AMP_DIN   22
  #define AMP_SD    -1
  #define LED_PIN   2    // встроенный светодиод
  #define AUDIO_BUF_BYTES (24 * 1024)
  #define SNAP_RING_MS    1200          // без PSRAM память дорогая: чуть больше буфера snapserver
  #define AMP_RATE        22050         // без PSRAM — моно 22050 Гц (стерео 44100 сводится в моно)
  #define AMP_STEREO      0
  #define MIC_AEC         0             // ESP-SR на обычном ESP32 нет
  #define MIC_COUNT       1
#endif

#define RESET_BUTTON 0     // кнопка BOOT/PROG: удерживать 5 секунд — сброс настроек Wi-Fi и комнаты

// ---------------- микрофон ----------------
// INMP441 отдаёт звук только в одном слоте I2S (L/R на GND — левый, на 3V3 — правый). Клиент читает оба слота:
// с одним микрофоном сам выбирает живой (в мониторе порта: «Микрофон: слот …»), с двумя (MIC_COUNT 2) — берёт оба.
// Два микрофона ставьте в 5–7 см друг от друга, отверстиями в одну сторону. -1 — автоматически; 0 или 1 — вручную.
#define MIC_SLOT          -1
#define DEFAULT_MIC_GAIN_DB 12   // начальное усиление микрофона, дБ (0..30)
#define DEFAULT_VAD_LEVEL   250  // порог речи (RMS). Меньше — чувствительнее, больше — меньше ложных срабатываний

// ---------------- автоусиление (АРУ) ----------------
// Медленная подстройка только по речи: после каждой фразы усиление сдвигается к цели,
// посреди фразы не меняется, шум не поднимается выше порога, при перегрузке — сразу вниз.
#define DEFAULT_AGC        1     // 1 — автоусиление включено
#define DEFAULT_AGC_MAX_DB 30    // верхняя граница автоусиления, дБ
#define AGC_TARGET         2500  // целевой уровень речи (хорошо распознаётся: 1500–5000)
#define AGC_STEP_MAX_DB    3.0f  // не больше стольких дБ за одну фразу
#define AGC_MIN_DB         6     // ниже автоусиление не опускается (ручное — можно до 0)
#define AGC_NOISE_MAX      400   // фоновый шум после усиления не выше этого: порог речи (шум × 3) остаётся ниже цели
#define AGC_CLIP_LEVEL     15000 // уровень фразы выше — искажения: усиление снижается без раздумий
#define AGC_CLIP_FRAMES    10    // столько кадров с перегрузкой за громкую фразу (0,2 с) — тоже снижаем
#define AGC_SAVE_MS        300000 // подобранное усиление сохраняется раз в 5 минут

// ---------------- детектор речи (VAD) ----------------
#define VAD_START_RATIO   3.0f   // во сколько раз громче фонового шума считается речью
#define VAD_START_FRAMES  3      // столько кадров по 20 мс подряд, чтобы начать
#define DEFAULT_VAD_HANG_MS 1000 // сколько тишины ждать до конца фразы (после "Руслана" — вдвое дольше)
#define VAD_PREROLL_MS    400    // сколько звука до начала речи отправить (чтобы не съесть начало слова)
#define VAD_MAX_MS        12000  // максимальная длина фразы
#define MIC_MUTE_AFTER_TTS_MS 350 // не слушать микрофон сразу после ответа (эхо)
#define METER_INTERVAL_MS 250    // живой индикатор для веб-интерфейса (шлётся, только пока страница открыта)

// ---------------- музыка (мультирум Snapcast) ----------------
// Клиент сам подключается к snapserver на том же адресе, что и сервер Русланы, с ID = ID комнаты.
// Какую музыку играет комната, решает Руслана (голосом: «добавь кухню», «как в спальне» — или на странице «Комнаты»).
#define SNAP_ENABLED     1       // 0 — клиент без музыки, как прошивка 2.x
#define SNAP_PORT        1704
#define MUSIC_DUCK_PCT   20      // громкость музыки, пока Руслана слушает команду и отвечает, % от обычной
#define MUSIC_VAD_RATIO  4.0f    // пока играет музыка без эхоподавления, речь должна быть во столько раз громче фона

// ---------------- эхо- и шумоподавление (ESP32-S3) ----------------
// Включаются и выключаются в веб-интерфейсе (вкладка «Комнаты»); здесь — значения по умолчанию.
#define DEFAULT_AEC      1       // эхоподавление: вычитать из микрофона музыку и голос своего динамика
#define DEFAULT_NS       1       // шумоподавление: убирать ровный фон
#define NS_MODE          1       // сила шумоподавления: 0 — мягко, 1 — средне, 2 — сильно (может портить речь)
#define MIC_REF_DELAY_US 0       // сдвиг опорного сигнала, мкс (динамик далеко от микрофона — например 3000)

// ---------------- обновление прошивки через сервер Русланы ----------------
#define OTA_CONFIRM_MS   180000  // новая прошивка не подключилась к серверу за 3 минуты — откат на прежнюю

// ---------------- Wi-Fi ----------------
// Если клиент перезагружается или теряет сеть, когда говорит (просадка питания) —
// попробуйте WIFI_POWER_15dBm. Если далеко от роутера — WIFI_POWER_19_5dBm (максимум).
#define WIFI_TX_POWER    WIFI_POWER_19_5dBm

#define DEFAULT_SERVER   "irene.local"
#define DEFAULT_PORT     8765
#define DEFAULT_VOLUME   70
// Предел громкости усилителя, % от полной. На 100% динамик 4 Ом берёт пики больше 1 А по 5 В —
// слабый блок питания или тонкий кабель просаживаются, и модуль перезагружается (brownout).
// С хорошим блоком 5 В 2 А и коротким толстым проводом можно поставить 100.
#define VOLUME_LIMIT_PCT 80
